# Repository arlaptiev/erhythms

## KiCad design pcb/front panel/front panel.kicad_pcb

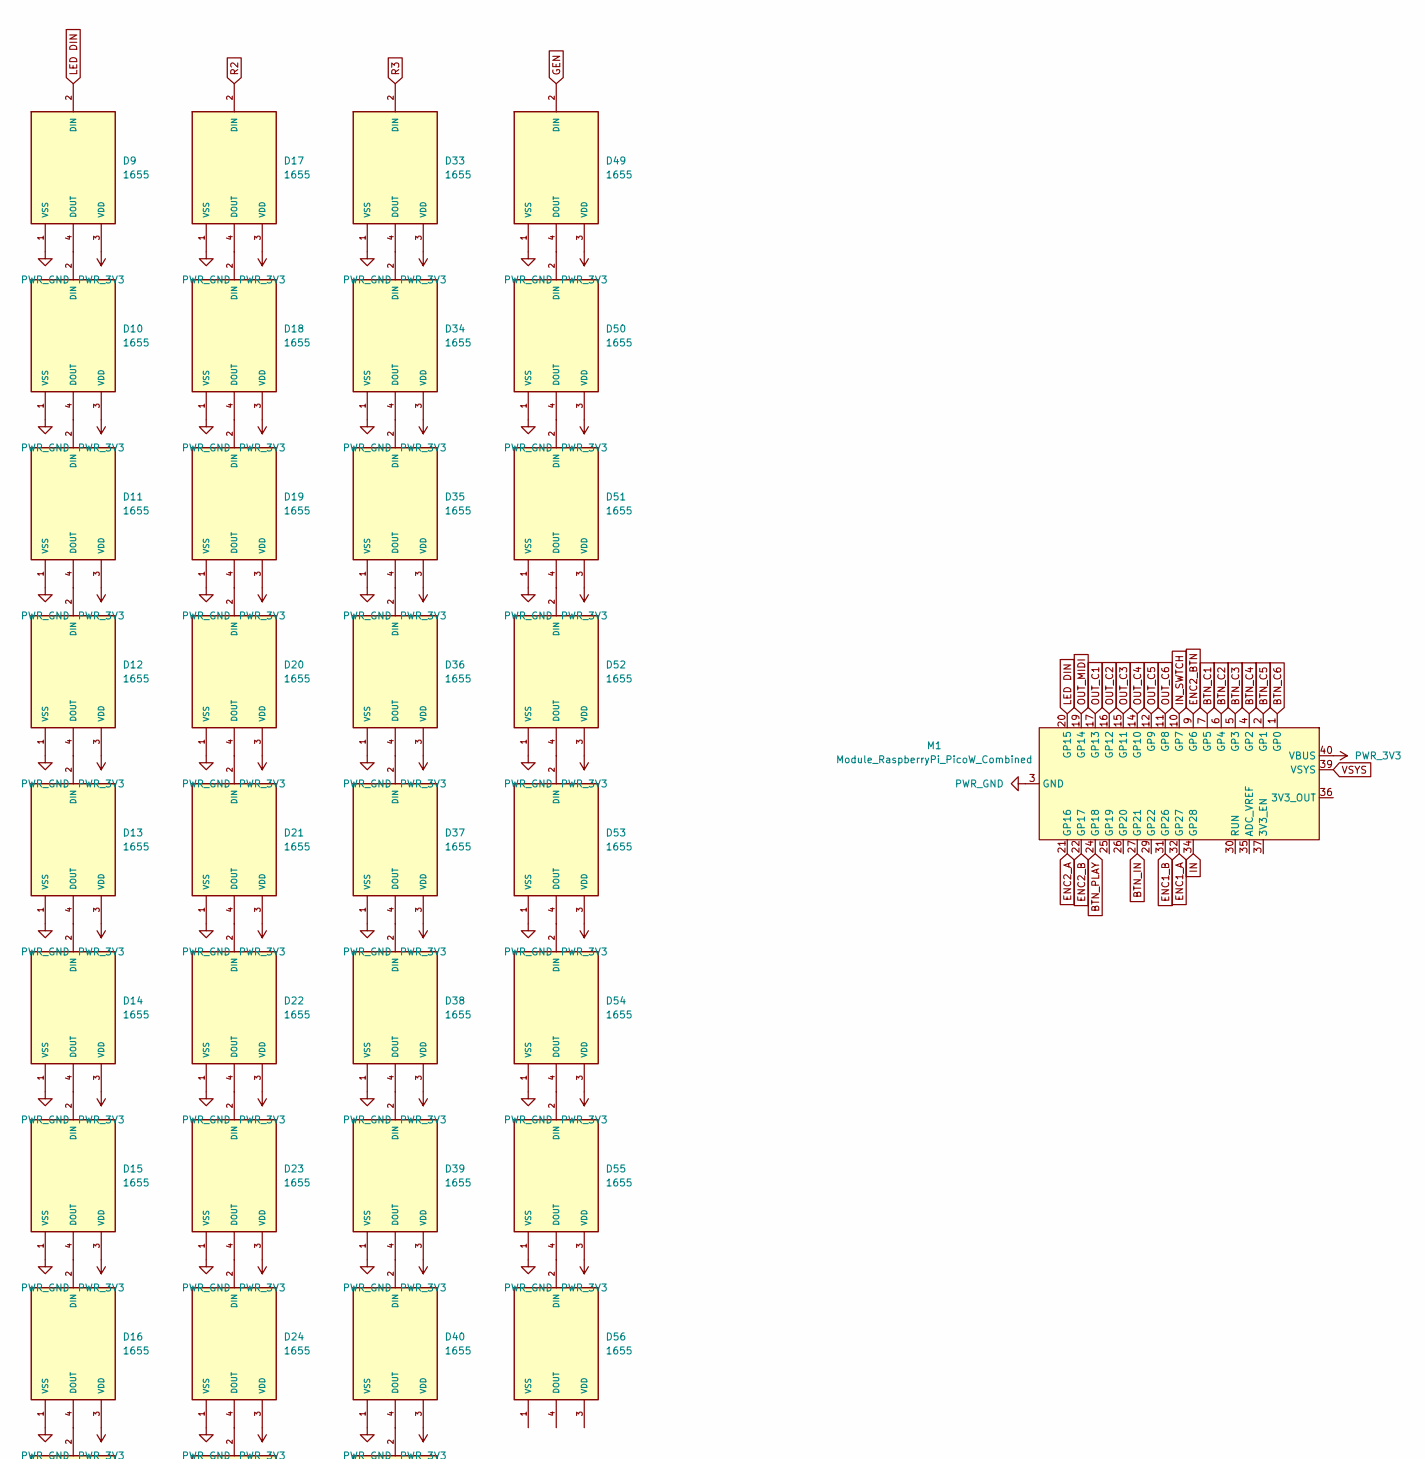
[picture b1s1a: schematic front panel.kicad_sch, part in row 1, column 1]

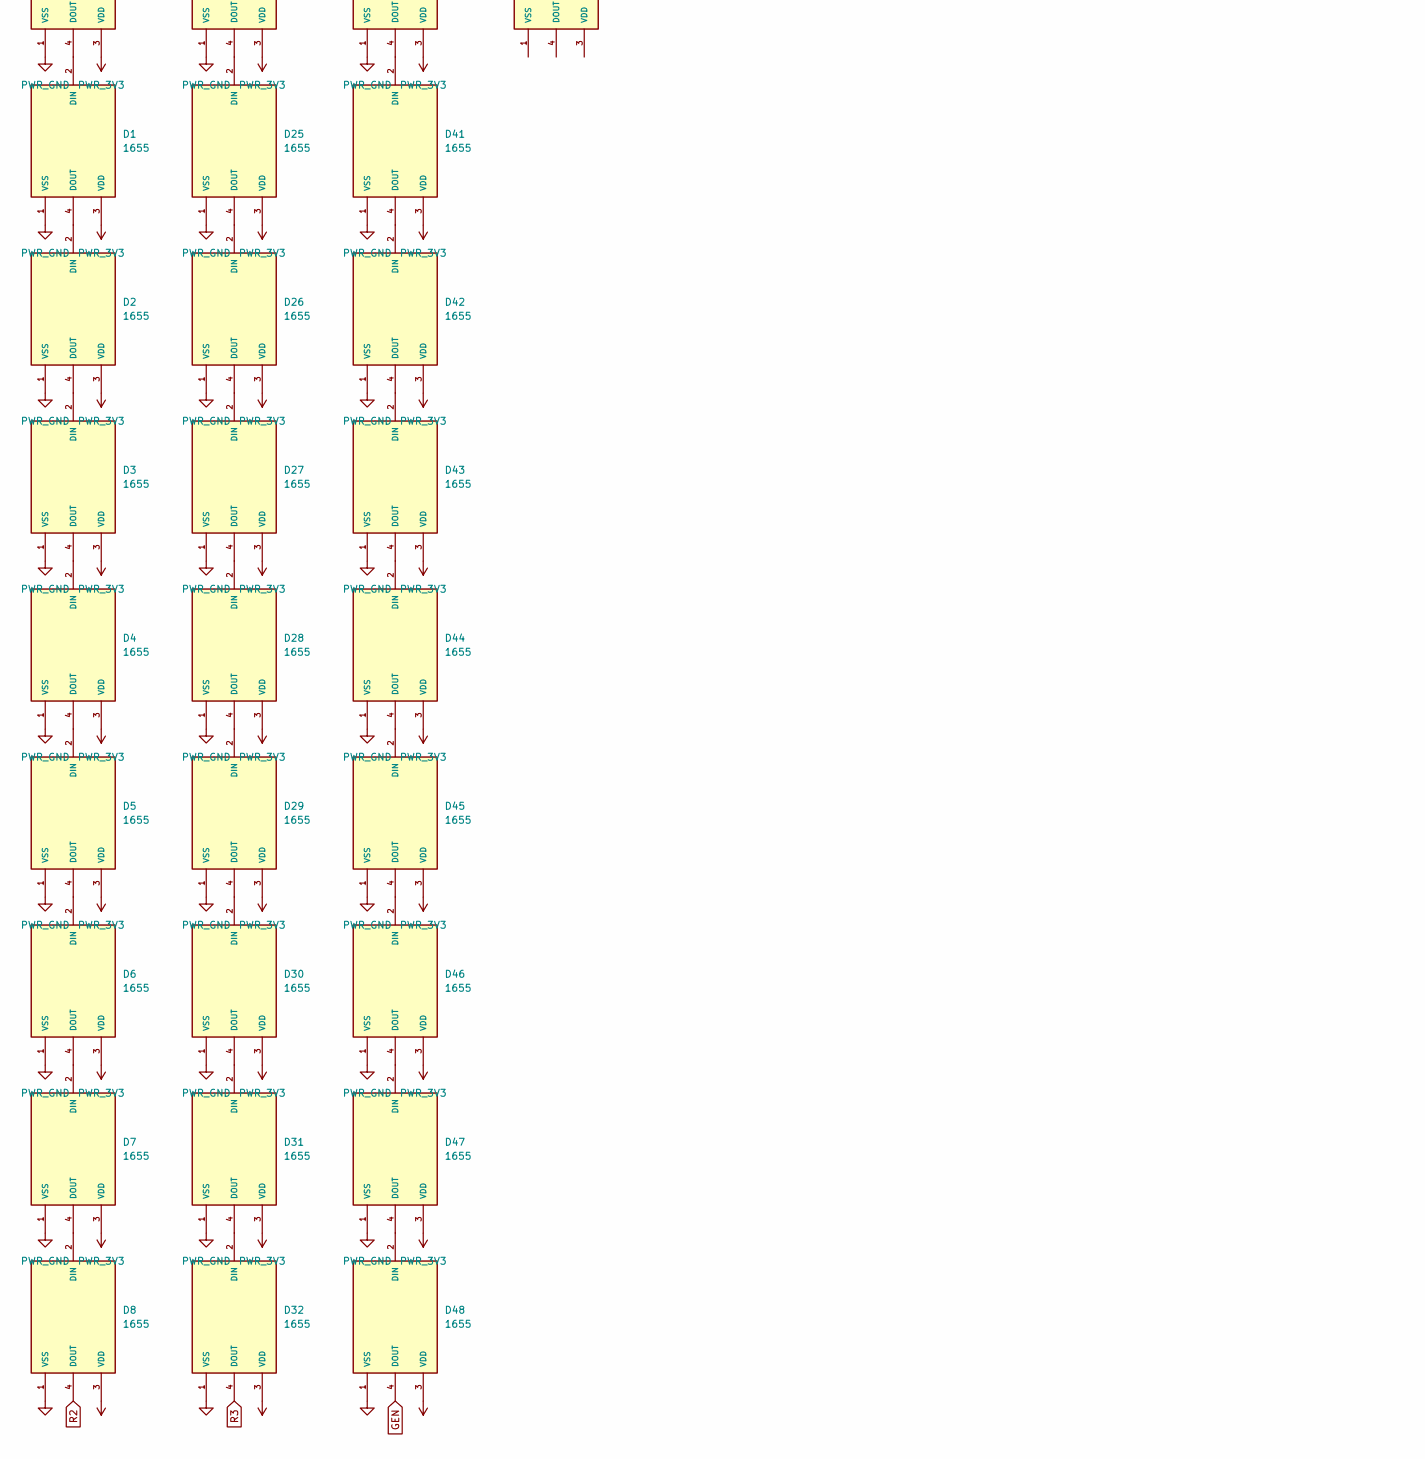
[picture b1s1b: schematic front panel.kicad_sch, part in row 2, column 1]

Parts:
D1, D2, D3, D4, D5, D6, D7, D8, D9, D10, D11, D12, D13, D14, D15, D16, D17, D18, D19, D20, D21, D22, D23, D24, D25, D26, D27, D28, D29, D30, D31, D32, D33, D34, D35, D36, D37, D38, D39, D40, D41, D42, D43, D44, D45, D46, D47, D48, D49, D50, D51, D52, D53, D54, D55, D56: 1655; LED_1655; PARTREV 01
M1: Module_RaspberryPi_PicoW_Combined; RaspberryPi_PicoW_Combined

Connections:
BTN_C1: M1.7 (GP5)
BTN_C2: M1.6 (GP4)
BTN_C3: M1.5 (GP3)
BTN_C4: M1.4 (GP2)
BTN_C5: M1.2 (GP1)
BTN_C6: M1.1 (GP0)
BTN_IN: M1.27 (GP21)
BTN_PLAY: M1.24 (GP18)
ENC1_A: M1.32 (GP27)
ENC1_B: M1.31 (GP26)
ENC2_A: M1.21 (GP16)
ENC2_B: M1.22 (GP17)
ENC2_BTN: M1.9 (GP6)
GEN: D48.4 (DOUT), D49.2 (DIN)
IN: M1.34 (GP28)
IN_SWTCH: M1.10 (GP7)
LED DIN: D9.2 (DIN), M1.20 (GP15)
unnamed: D1.2 (DIN), D16.4 (DOUT)
unnamed: D1.4 (DOUT), D2.2 (DIN)
unnamed: D2.4 (DOUT), D3.2 (DIN)
unnamed: D3.4 (DOUT), D4.2 (DIN)
unnamed: D4.4 (DOUT), D5.2 (DIN)
unnamed: D5.4 (DOUT), D6.2 (DIN)
unnamed: D6.4 (DOUT), D7.2 (DIN)
unnamed: D7.4 (DOUT), D8.2 (DIN)
unnamed: D9.4 (DOUT), D10.2 (DIN)
unnamed: D10.4 (DOUT), D11.2 (DIN)
unnamed: D11.4 (DOUT), D12.2 (DIN)
unnamed: D12.4 (DOUT), D13.2 (DIN)
unnamed: D13.4 (DOUT), D14.2 (DIN)
unnamed: D14.4 (DOUT), D15.2 (DIN)
unnamed: D15.4 (DOUT), D16.2 (DIN)
unnamed: D17.4 (DOUT), D18.2 (DIN)
unnamed: D18.4 (DOUT), D19.2 (DIN)
unnamed: D19.4 (DOUT), D20.2 (DIN)
unnamed: D20.4 (DOUT), D21.2 (DIN)
unnamed: D21.4 (DOUT), D22.2 (DIN)
unnamed: D22.4 (DOUT), D23.2 (DIN)
unnamed: D23.4 (DOUT), D24.2 (DIN)
unnamed: D24.4 (DOUT), D25.2 (DIN)
unnamed: D25.4 (DOUT), D26.2 (DIN)
unnamed: D26.4 (DOUT), D27.2 (DIN)
unnamed: D27.4 (DOUT), D28.2 (DIN)
unnamed: D28.4 (DOUT), D29.2 (DIN)
unnamed: D29.4 (DOUT), D30.2 (DIN)
unnamed: D30.4 (DOUT), D31.2 (DIN)
unnamed: D31.4 (DOUT), D32.2 (DIN)
unnamed: D33.4 (DOUT), D34.2 (DIN)
unnamed: D34.4 (DOUT), D35.2 (DIN)
unnamed: D35.4 (DOUT), D36.2 (DIN)
unnamed: D36.4 (DOUT), D37.2 (DIN)
unnamed: D37.4 (DOUT), D38.2 (DIN)
unnamed: D38.4 (DOUT), D39.2 (DIN)
unnamed: D39.4 (DOUT), D40.2 (DIN)
unnamed: D40.4 (DOUT), D41.2 (DIN)
unnamed: D41.4 (DOUT), D42.2 (DIN)
unnamed: D42.4 (DOUT), D43.2 (DIN)
unnamed: D43.4 (DOUT), D44.2 (DIN)
unnamed: D44.4 (DOUT), D45.2 (DIN)
unnamed: D45.4 (DOUT), D46.2 (DIN)
unnamed: D46.4 (DOUT), D47.2 (DIN)
unnamed: D47.4 (DOUT), D48.2 (DIN)
unnamed: D49.4 (DOUT), D50.2 (DIN)
unnamed: D50.4 (DOUT), D51.2 (DIN)
unnamed: D51.4 (DOUT), D52.2 (DIN)
unnamed: D52.4 (DOUT), D53.2 (DIN)
unnamed: D53.4 (DOUT), D54.2 (DIN)
unnamed: D54.4 (DOUT), D55.2 (DIN)
unnamed: D55.4 (DOUT), D56.2 (DIN)
OUT_C1: M1.17 (GP13)
OUT_C2: M1.16 (GP12)
OUT_C3: M1.15 (GP11)
OUT_C4: M1.14 (GP10)
OUT_C5: M1.12 (GP9)
OUT_C6: M1.11 (GP8)
OUT_MIDI: M1.19 (GP14)
PWR_3V3: D1.3 (VDD), D2.3 (VDD), D3.3 (VDD), D4.3 (VDD), D5.3 (VDD), D6.3 (VDD), D7.3 (VDD), D8.3 (VDD), D9.3 (VDD), D10.3 (VDD), D11.3 (VDD), D12.3 (VDD), D13.3 (VDD), D14.3 (VDD), D15.3 (VDD), D16.3 (VDD), D17.3 (VDD), D18.3 (VDD), D19.3 (VDD), D20.3 (VDD), D21.3 (VDD), D22.3 (VDD), D23.3 (VDD), D24.3 (VDD), D25.3 (VDD), D26.3 (VDD), D27.3 (VDD), D28.3 (VDD), D29.3 (VDD), D30.3 (VDD), D31.3 (VDD), D32.3 (VDD), D33.3 (VDD), D34.3 (VDD), D35.3 (VDD), D36.3 (VDD), D37.3 (VDD), D38.3 (VDD), D39.3 (VDD), D40.3 (VDD), D41.3 (VDD), D42.3 (VDD), D43.3 (VDD), D44.3 (VDD), D45.3 (VDD), D46.3 (VDD), D47.3 (VDD), D48.3 (VDD), D49.3 (VDD), D50.3 (VDD), D51.3 (VDD), D52.3 (VDD), D53.3 (VDD), D54.3 (VDD), D55.3 (VDD), M1.36 (3V3_OUT), M1.40 (VBUS)
PWR_GND: D1.1 (VSS), D2.1 (VSS), D3.1 (VSS), D4.1 (VSS), D5.1 (VSS), D6.1 (VSS), D7.1 (VSS), D8.1 (VSS), D9.1 (VSS), D10.1 (VSS), D11.1 (VSS), D12.1 (VSS), D13.1 (VSS), D14.1 (VSS), D15.1 (VSS), D16.1 (VSS), D17.1 (VSS), D18.1 (VSS), D19.1 (VSS), D20.1 (VSS), D21.1 (VSS), D22.1 (VSS), D23.1 (VSS), D24.1 (VSS), D25.1 (VSS), D26.1 (VSS), D27.1 (VSS), D28.1 (VSS), D29.1 (VSS), D30.1 (VSS), D31.1 (VSS), D32.1 (VSS), D33.1 (VSS), D34.1 (VSS), D35.1 (VSS), D36.1 (VSS), D37.1 (VSS), D38.1 (VSS), D39.1 (VSS), D40.1 (VSS), D41.1 (VSS), D42.1 (VSS), D43.1 (VSS), D44.1 (VSS), D45.1 (VSS), D46.1 (VSS), D47.1 (VSS), D48.1 (VSS), D49.1 (VSS), D50.1 (VSS), D51.1 (VSS), D52.1 (VSS), D53.1 (VSS), D54.1 (VSS), D55.1 (VSS), M1.3 (GND), M1.8 (GND), M1.13 (GND), M1.18 (GND), M1.23 (GND), M1.28 (GND), M1.33 (GND), M1.38 (GND)
R2: D8.4 (DOUT), D17.2 (DIN)
R3: D32.4 (DOUT), D33.2 (DIN)
VSYS: M1.39 (VSYS)

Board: 2 copper layers, 76 parts (0 on the bottom side), 58 nets, no tracks yet.

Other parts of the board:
J1, J2, J3, J4, J5, J6, J7, J8: FC681374V; CLIFF_FC681374V
J9: PJ-064A; CUI_PJ-064A
MT1, MT2: PEC11R-4215F-S0024; XDCR_PEC11R-4215F-S0024
S1: 100SP1T1B1M1QEH; SW_100SP1T1B1M1QEH
SW1, SW3, SW4, SW5, SW6, SW7, SW8: Switch_Tactile_CnK; MX1A-11NW

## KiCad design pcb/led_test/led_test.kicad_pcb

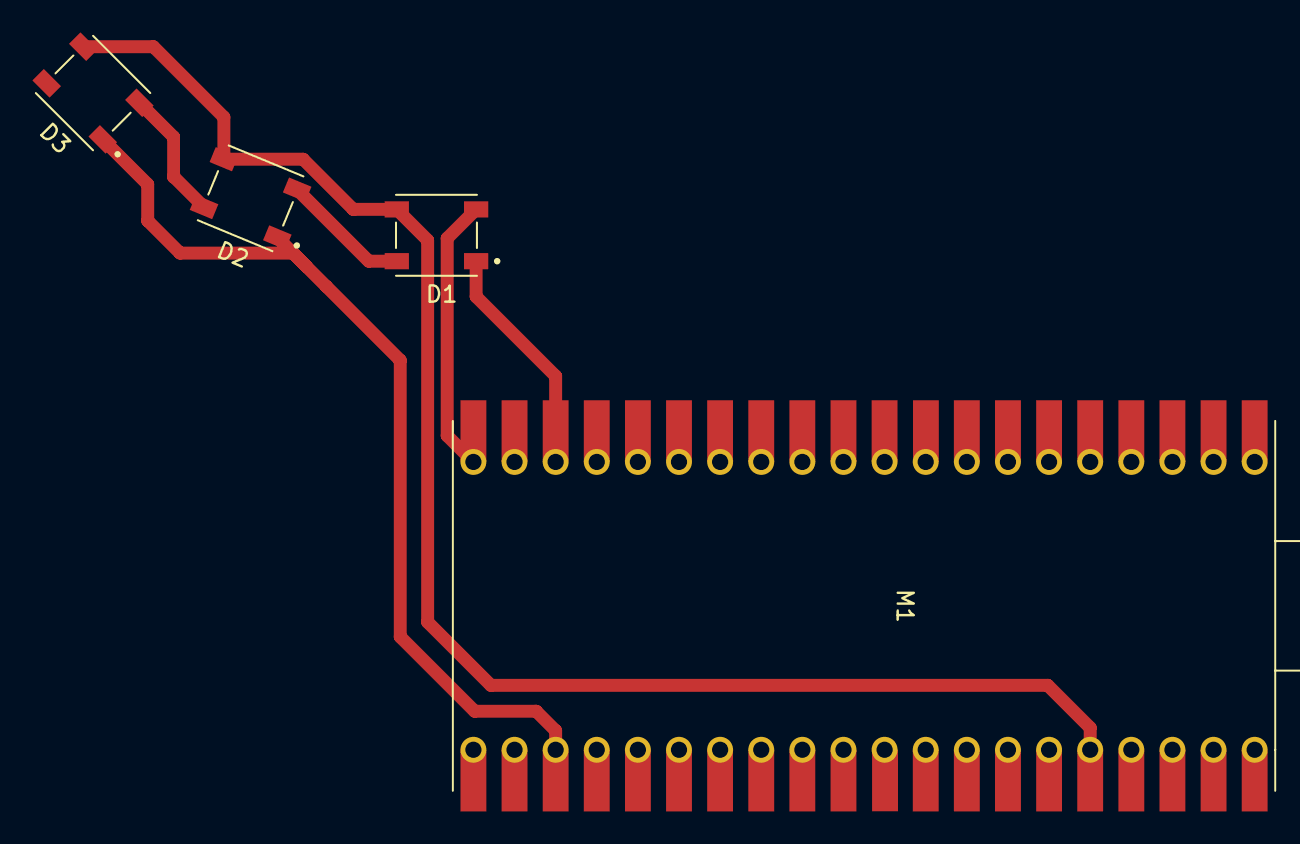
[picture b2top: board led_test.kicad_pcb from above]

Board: 2 copper layers, 4 parts (0 on the bottom side), 5 nets.

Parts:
D1, D2, D3: 1655; LED_1655
M1: Module_RaspberryPi_PicoW_Combined; RaspberryPi_PicoW_Combined

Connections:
LED DIN: D1.2 (DIN), M1.20 (GP15)
unnamed: D1.4 (DOUT), D2.2 (DIN)
unnamed: D2.4 (DOUT), D3.2 (DIN)
PWR_3V3: D1.3 (VDD), D2.3 (VDD), D3.3 (VDD), M1.36 (3V3_OUT)
PWR_GND: D1.1 (VSS), D2.1 (VSS), D3.1 (VSS), M1.3 (GND), M1.8 (GND), M1.13 (GND), M1.18 (GND), M1.23 (GND), M1.28 (GND), M1.33 (GND), M1.38 (GND)

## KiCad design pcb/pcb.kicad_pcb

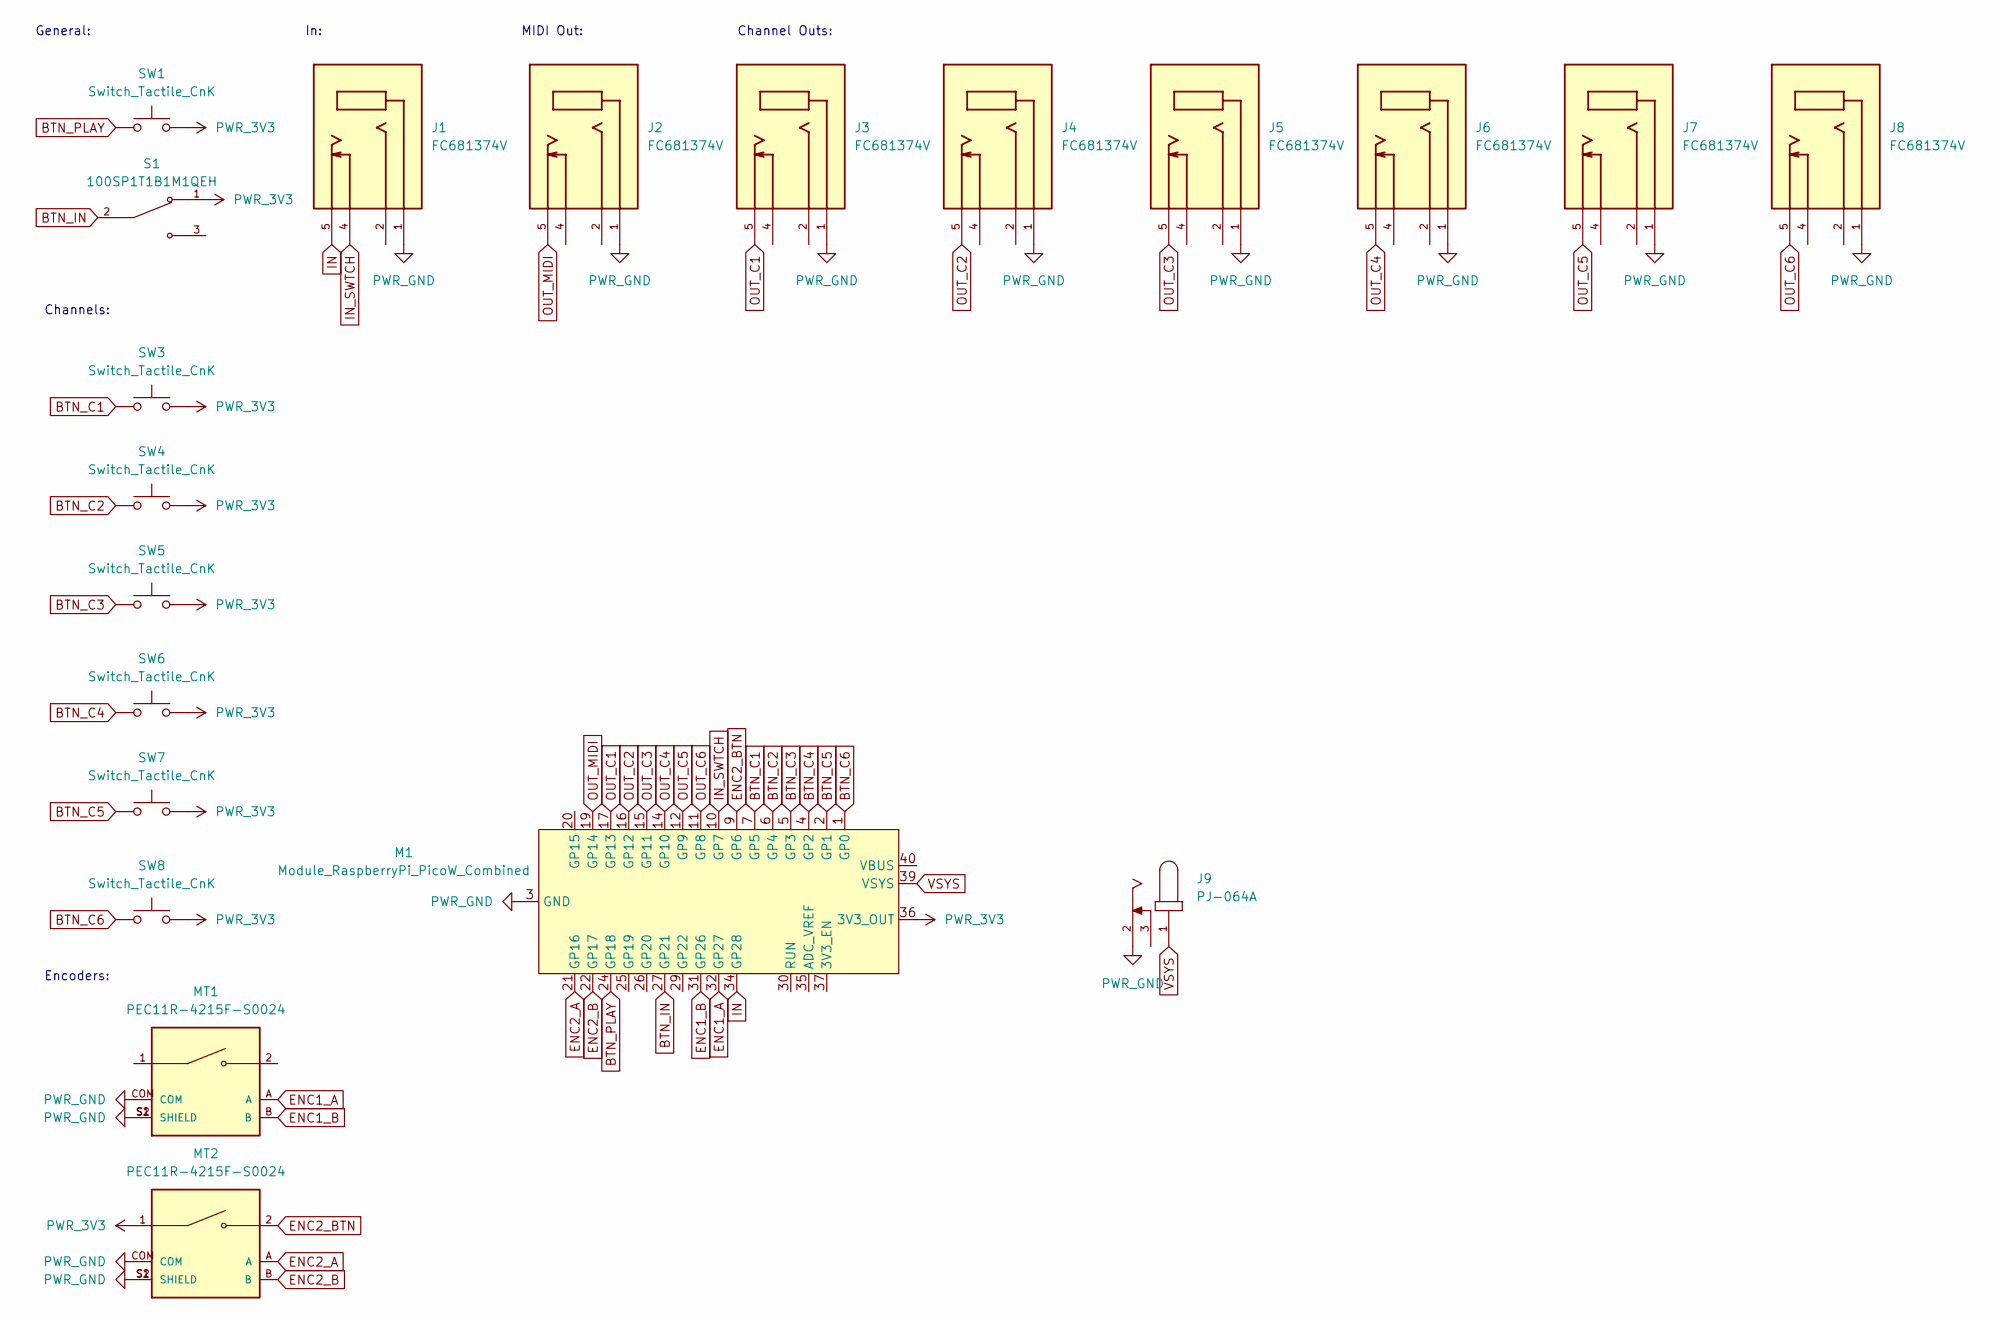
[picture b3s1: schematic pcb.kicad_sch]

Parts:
J1, J2, J3, J4, J5, J6, J7, J8: FC681374V; CLIFF_FC681374V
J9: PJ-064A; CUI_PJ-064A; PARTREV 1.02
M1: Module_RaspberryPi_PicoW_Combined; RaspberryPi_PicoW_Combined
MT1, MT2: PEC11R-4215F-S0024; XDCR_PEC11R-4215F-S0024; PARTREV Rev. 09/19
S1: 100SP1T1B1M1QEH; SW_100SP1T1B1M1QEH; PARTREV D
SW1, SW3, SW4, SW5, SW6, SW7, SW8: Switch_Tactile_CnK; MX1A-11NW

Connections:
BTN_C1: M1.7 (GP5), SW3.1
BTN_C2: M1.6 (GP4), SW4.1
BTN_C3: M1.5 (GP3), SW5.1
BTN_C4: M1.4 (GP2), SW6.1
BTN_C5: M1.2 (GP1), SW7.1
BTN_C6: M1.1 (GP0), SW8.1
BTN_IN: M1.27 (GP21), S1.2
BTN_PLAY: M1.24 (GP18), SW1.1
ENC1_A: M1.32 (GP27), MT1.A
ENC1_B: M1.31 (GP26), MT1.B
ENC2_A: M1.21 (GP16), MT2.A
ENC2_B: M1.22 (GP17), MT2.B
ENC2_BTN: M1.9 (GP6), MT2.2
IN: J1.5, M1.34 (GP28)
IN_SWTCH: J1.4, M1.10 (GP7)
OUT_C1: J3.5, M1.17 (GP13)
OUT_C2: J4.5, M1.16 (GP12)
OUT_C3: J5.5, M1.15 (GP11)
OUT_C4: J6.5, M1.14 (GP10)
OUT_C5: J7.5, M1.12 (GP9)
OUT_C6: J8.5, M1.11 (GP8)
OUT_MIDI: J2.5, M1.19 (GP14)
PWR_3V3: M1.36 (3V3_OUT), MT2.1, S1.1, SW1.2, SW3.2, SW4.2, SW5.2, SW6.2, SW7.2, SW8.2
PWR_GND: J1.1, J2.1, J3.1, J4.1, J5.1, J6.1, J7.1, J8.1, J9.2, M1.3 (GND), M1.8 (GND), M1.13 (GND), M1.18 (GND), M1.23 (GND), M1.28 (GND), M1.33 (GND), M1.38 (GND), MT1.COM, MT1.S1 (SHIELD), MT1.S2 (SHIELD), MT2.COM, MT2.S1 (SHIELD), MT2.S2 (SHIELD)
VSYS: J9.1, M1.39 (VSYS)

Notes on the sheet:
General:
In:
MIDI Out:
Channel Outs:
Encoders:
Channels:

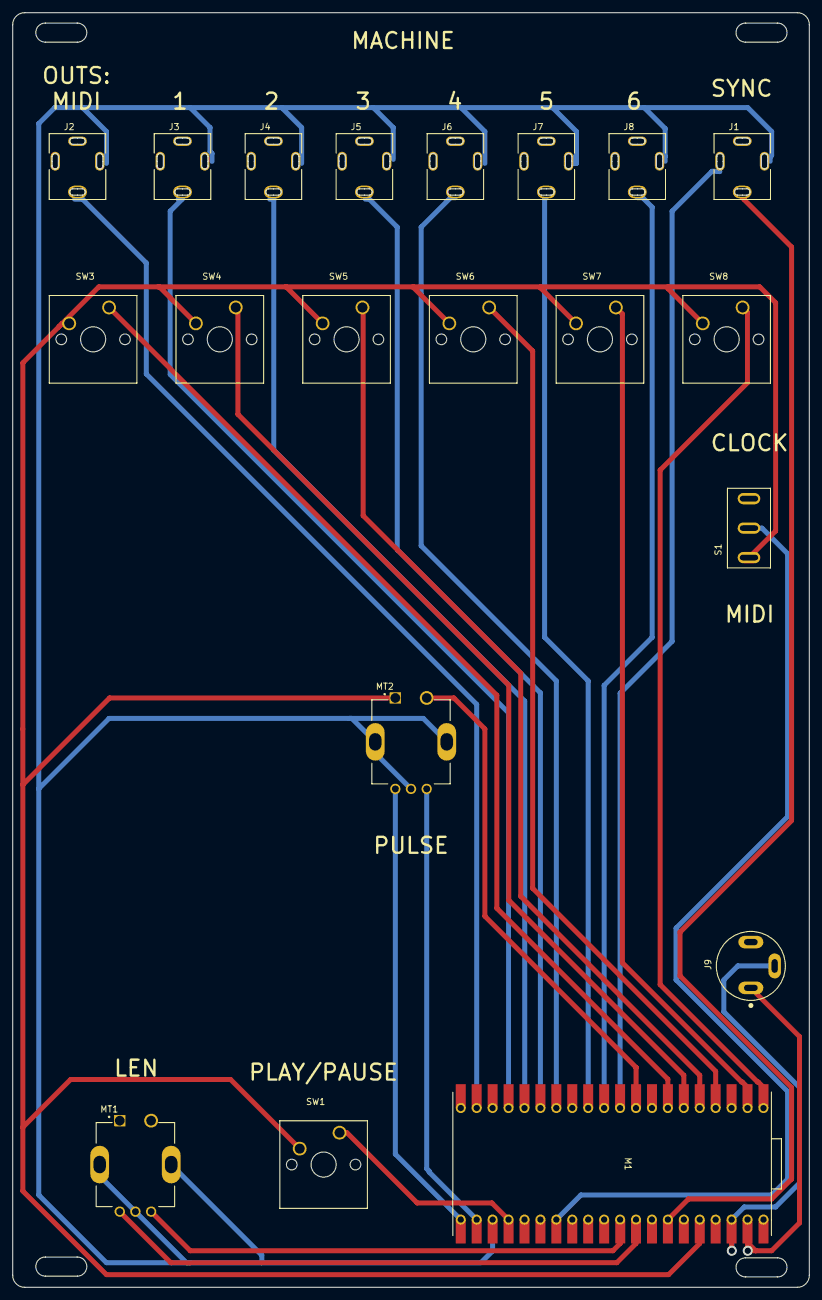
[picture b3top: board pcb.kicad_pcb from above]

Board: 2 copper layers, 127.0 x 203.2 mm, 20 parts (0 on the bottom side), 25 nets.

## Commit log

2023-12-07 init
2023-12-07 sequencer-ready
2023-12-16 controls-adapted+midi-progress
2023-12-16 organize
